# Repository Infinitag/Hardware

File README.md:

# INFINITAG Hardware

All hardware files for the INFINITAG laser tag system

## Credits
Website: <http://www.infinitag.io>

## License
All files are published under Creative Commons Attribution-NonCommercial-ShareAlike 4.0 International (CC BY-NC-SA 4.0) License
<https://creativecommons.org/licenses/by-nc-sa/4.0/>

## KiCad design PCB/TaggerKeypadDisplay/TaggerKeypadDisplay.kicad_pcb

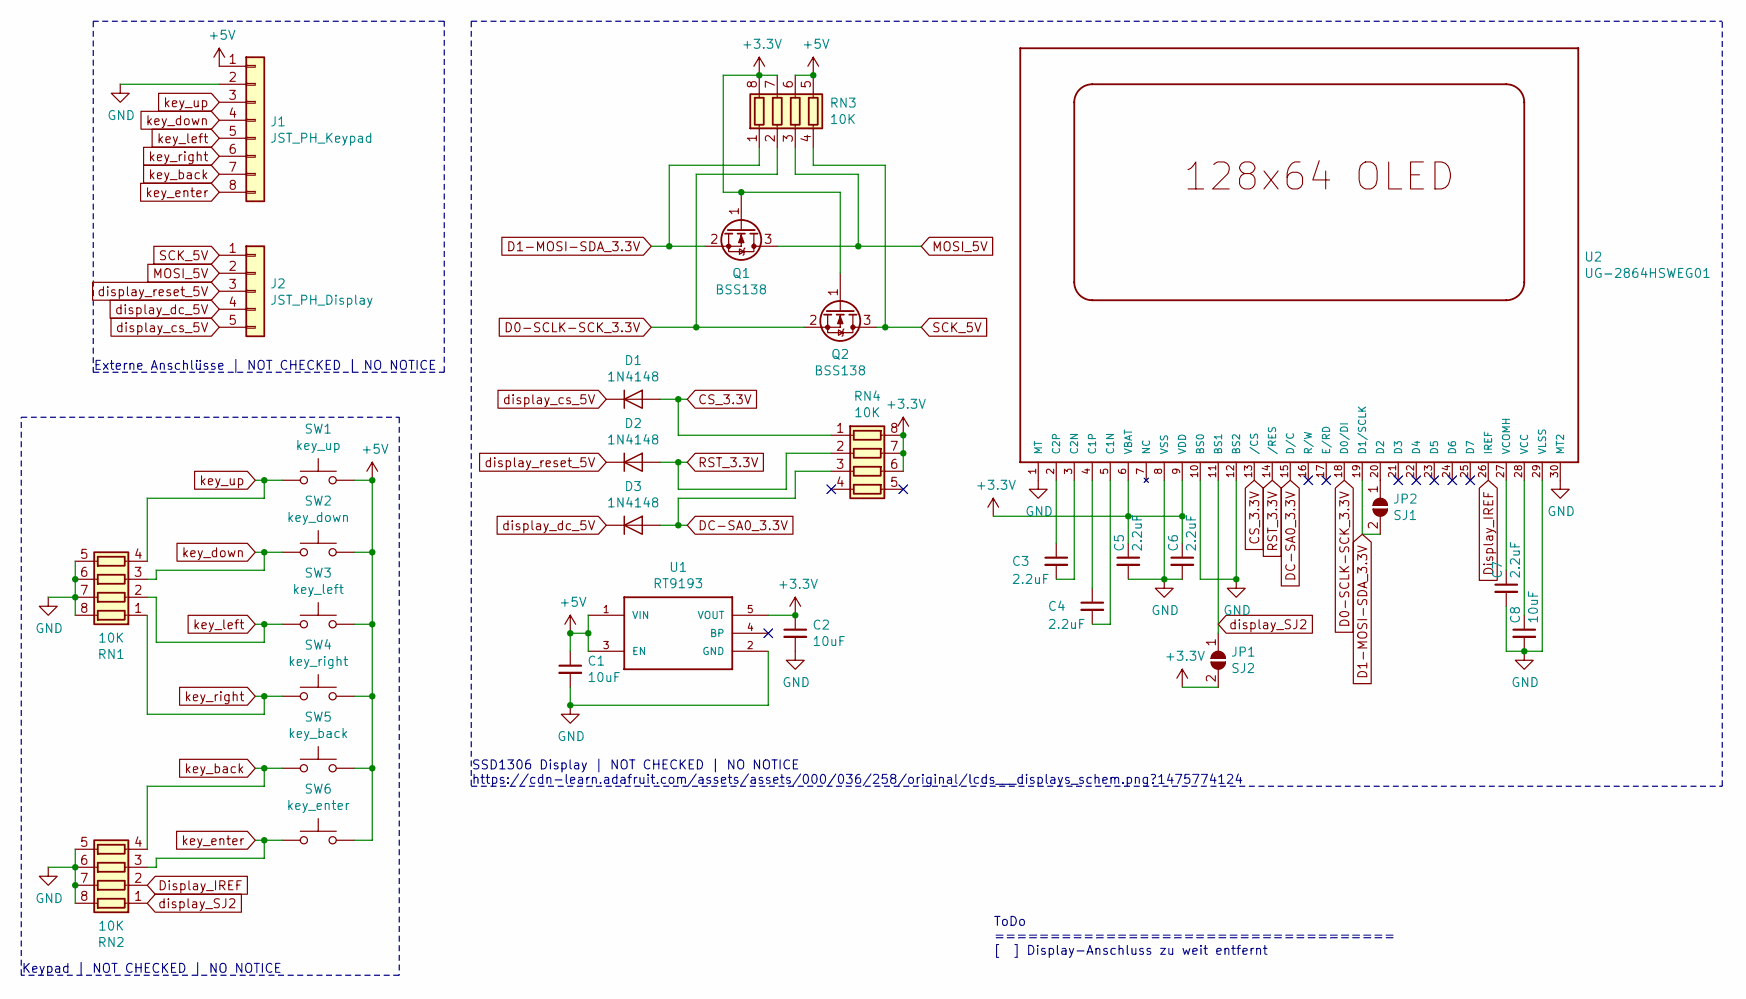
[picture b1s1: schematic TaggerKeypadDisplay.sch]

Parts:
C1, C2, C8: 10uF; C_0805_2012Metric
C3, C4, C5, C6, C7: 2.2uF; C_0805_2012Metric
D1, D2, D3: 1N4148; D_SOD-123
J1: JST_PH_Keypad; JST_PH_B8B-PH-K_1x08_P2.00mm_Vertical
J2: JST_PH_Display; JST_PH_B5B-PH-K_1x05_P2.00mm_Vertical
JP1: SJ2; SolderJumper-2_P1.3mm_Open_Pad1.0x1.5mm
JP2: SJ1; SolderJumper-2_P1.3mm_Open_Pad1.0x1.5mm
Q1, Q2: BSS138; SOT-23
RN1, RN2, RN3, RN4: 10K; R_Array_Convex_4x0603
SW1: key_up; Infinitag_Keypad_Button
SW2: key_down; Infinitag_Keypad_Button
SW3: key_left; Infinitag_Keypad_Button
SW4: key_right; Infinitag_Keypad_Button
SW5: key_back; Infinitag_Keypad_Button
SW6: key_enter; Infinitag_Keypad_Button
U1: RT9193; SOT94P279X129-5N
U2: UG-2864HSWEG01; 1X30-0.7MM

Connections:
+3V3: C2.1, C5.1, C6.1, JP1.2 (B), Q1.1 (G), Q2.1 (G), RN3.7 (R2.2), RN3.8 (R1.2), RN4.6 (R3.2), RN4.7 (R2.2), RN4.8 (R1.2), U1.5 (VOUT), U2.6 (VBAT), U2.9 (VDD)
+5V: C1.1, J1.1, RN3.5 (R4.2), RN3.6 (R3.2), SW1.2, SW2.2, SW3.2, SW4.2, SW5.2, SW6.2, U1.1 (VIN), U1.3 (EN)
CS_3.3V: D1.2 (A), RN4.1 (R1.1), U2.13 (/CS)
D0-SCLK-SCK_3.3V: Q2.2 (S), RN3.2 (R2.1), U2.18 (D0/DI)
D1-MOSI-SDA_3.3V: JP2.2 (B), Q1.2 (S), RN3.1 (R1.1), U2.19 (D1/SCLK)
DC-SA0_3.3V: D3.2 (A), RN4.3 (R3.1), U2.15 (D/C)
Display_IREF: RN2.2 (R2.1), U2.26 (IREF)
GND: C1.2, C2.2, C5.2, C6.2, C7.2, C8.2, J1.2, RN1.5 (R4.2), RN1.6 (R3.2), RN1.7 (R2.2), RN1.8 (R1.2), RN2.5 (R4.2), RN2.6 (R3.2), RN2.7 (R2.2), RN2.8 (R1.2), U1.2 (GND), U2.1 (MT), U2.8 (VSS), U2.10 (BS0), U2.12 (BS2), U2.29 (VLSS), U2.30 (MT2)
MOSI_5V: J2.2, Q1.3 (D), RN3.3 (R3.1)
unnamed: C3.1, U2.2 (C2P)
unnamed: C3.2, U2.3 (C2N)
unnamed: C4.1, U2.4 (C1P)
unnamed: C4.2, U2.5 (C1N)
unnamed: C7.1, U2.27 (VCOMH)
unnamed: C8.1, U2.28 (VCC)
unnamed: JP2.1 (A), U2.20 (D2)
RST_3.3V: D2.2 (A), RN4.2 (R2.1), U2.14 (/RES)
SCK_5V: J2.1, Q2.3 (D), RN3.4 (R4.1)
display_SJ2: JP1.1 (A), RN2.1 (R1.1), U2.11 (BS1)
display_cs_5V: D1.1 (K), J2.5
display_dc_5V: D3.1 (K), J2.4
display_reset_5V: D2.1 (K), J2.3
key_back: J1.7, RN2.4 (R4.1), SW5.1
key_down: J1.4, RN1.3 (R3.1), SW2.1
key_enter: J1.8, RN2.3 (R3.1), SW6.1
key_left: J1.5, RN1.2 (R2.1), SW3.1
key_right: J1.6, RN1.1 (R1.1), SW4.1
key_up: J1.3, RN1.4 (R4.1), SW1.1

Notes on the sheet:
Externe Anschlüsse | NOT CHECKED | NO NOTICE
SSD1306 Display | NOT CHECKED | NO NOTICE https://cdn-learn.adafruit.com/assets/assets/000/036/258/original/lcds___displays_schem.png?1475774124
Keypad | NOT CHECKED | NO NOTICE
ToDo ==================================== [ ] Display-Anschluss zu weit entfernt

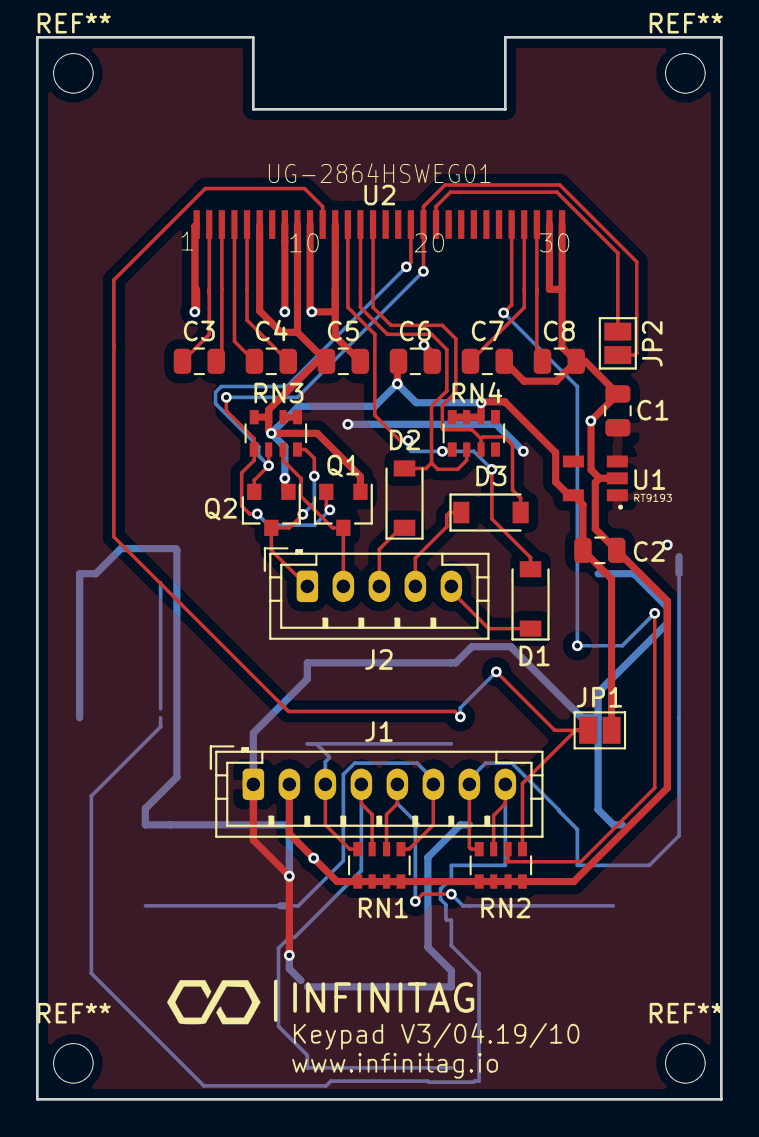
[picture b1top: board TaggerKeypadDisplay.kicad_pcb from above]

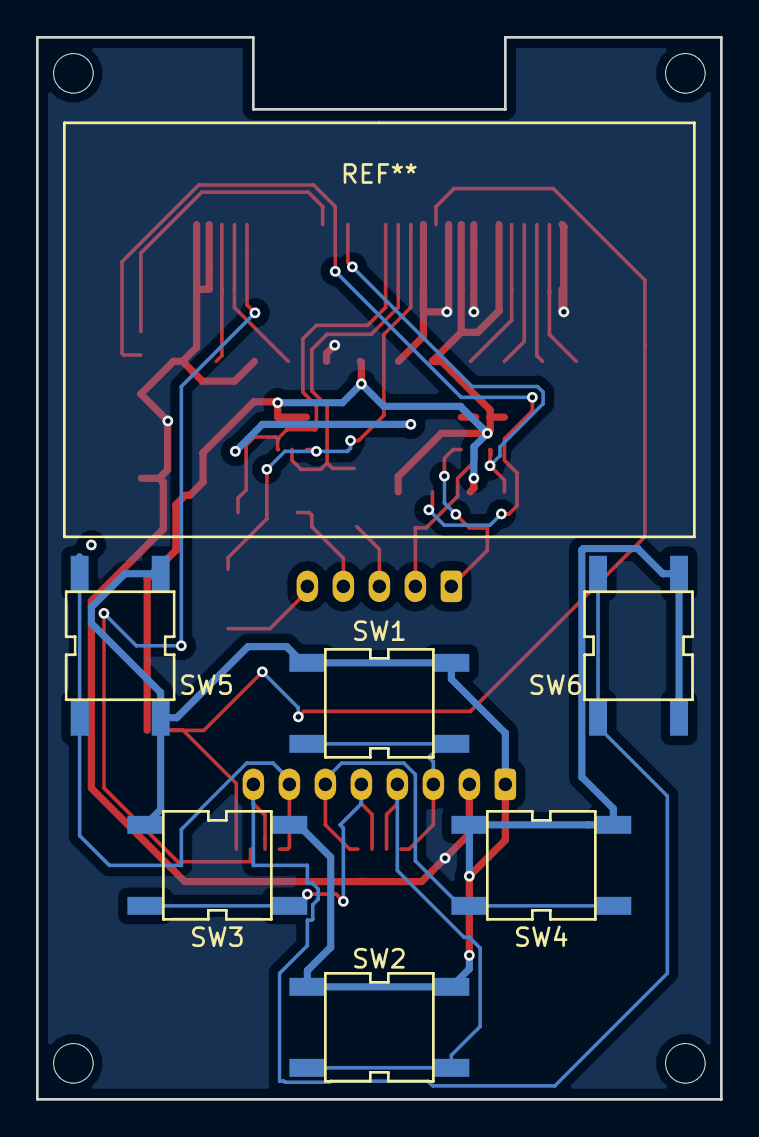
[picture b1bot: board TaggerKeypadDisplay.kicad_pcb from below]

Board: 2 copper layers, 38.0 x 59.0 mm, 29 parts (6 on the bottom side), 28 nets.

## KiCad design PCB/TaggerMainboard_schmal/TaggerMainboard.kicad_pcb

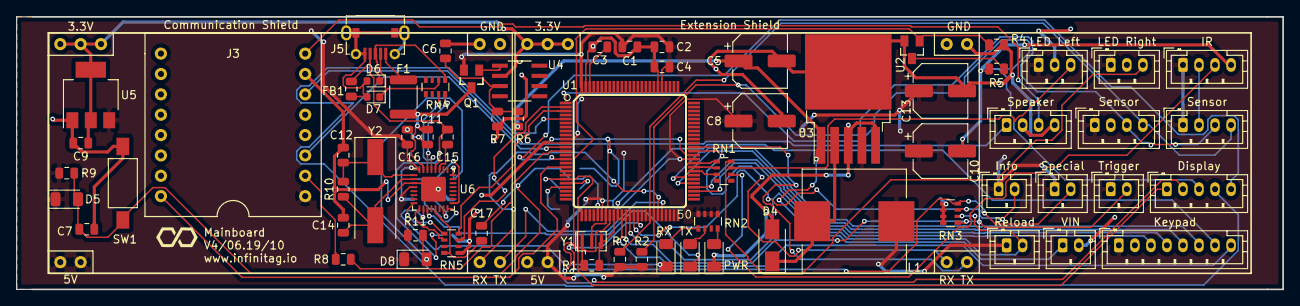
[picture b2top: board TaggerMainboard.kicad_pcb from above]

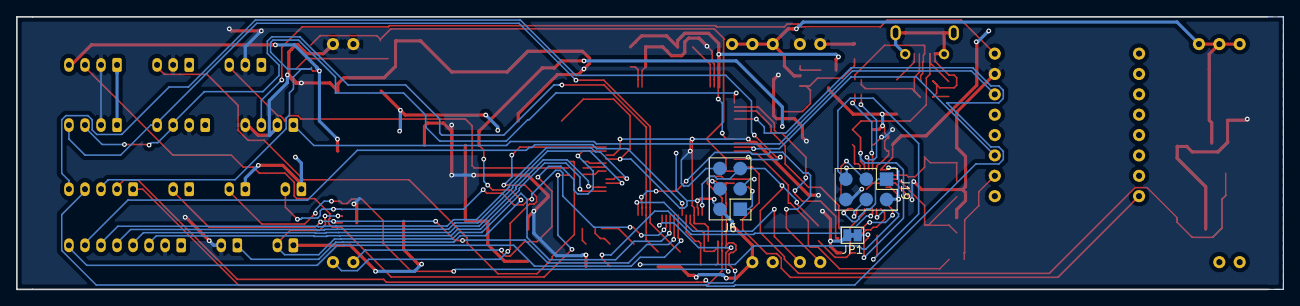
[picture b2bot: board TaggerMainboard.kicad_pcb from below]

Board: 2 copper layers, 158.0 x 34.0 mm, 74 parts (3 on the bottom side), 73 nets.

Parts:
C1, C2, C3, C4, C6, C17: 100nF; C_0805_2012Metric
C5, C8, C10, C13: 220uF/16V; CP_Elec_6.3x5.8
C7: 22pF; C_0805_2012Metric
C9: 10uF; C_0805_2012Metric
C11, C16: 100n; C_0805_2012Metric
C12, C14: 22p; C_0805_2012Metric
C15: 1u; C_0805_2012Metric
Communication Shield: WiFi Connector; Infinitag_ESP_Shield_Lang
D4: S534; D_SMA
D5, D8: CD1206-S01575; D_1206_3216Metric
D6, D7: CG0603MLC-05E; D_0603_1608Metric
Display: JST_PH_Display; JST_PH_B5B-PH-K_1x05_P2.00mm_Vertical
Extension Shield: Infinitag_ESP_Shield_Lang
F1: Poly 500mA; Fuse_1812_4532Metric
FB1: BLM21PG 221; L_0805_2012Metric
IR: JST_PH_IrLED; JST_PH_B4B-PH-K_1x04_P2.00mm_Vertical
Info: JST_PH_Info; JST_PH_B2B-PH-K_1x02_P2.00mm_Vertical
J3: DFPlayer
J5: USB_OTG; Micro USB Jack
J6: ICSP; ICSP_Pogo
J19: Conn_02x03_Odd_Even; ICSP_Pogo
JP1: SolderJumper_2_Bridged; SolderJumper-2_P1.3mm_Bridged_Pad1.0x1.5mm
Keypad: JST_PH_Keypad; JST_PH_B8B-PH-K_1x08_P2.00mm_Vertical
L1: 330uH; L_Wuerth_HCI-1350
LED Left: JST_PH_LEDbar_left; JST_PH_B3B-PH-K_1x03_P2.00mm_Vertical
LED Right: JST_PH_LEDbar_right; JST_PH_B3B-PH-K_1x03_P2.00mm_Vertical
PWR: LED_green; LED_1206_3216Metric
Q1: FDN304P; SSOT-3
R1, R10: 1M; R_0805_2012Metric
R2, R3, R4, R6, R7, R9, R11: 10K; R_0805_2012Metric
R5: 50 Ohm; R_0805_2012Metric
R8: 1K; R_0805_2012Metric
RN1: Array 470; R_Array_Convex_4x0603
RN2, RN3: Array 10K; R_Array_Convex_4x0603
RN4: 22R; R_Array_Convex_4x0603
RN5: 1K; R_Array_Convex_4x0603
RX: LED_RX_red; LED_1206_3216Metric
Reload: JST_PH_Reload; JST_PH_B2B-PH-K_1x02_P2.00mm_Vertical
SW1: SW_Reset; SW_SPST_FSMSM
Sensor: JSP_PH_Sensor; JST_PH_B4B-PH-K_1x04_P2.00mm_Vertical
Sensor#2: JSP_PH_Sensor; JST_PH_B4B-PH-K_1x04_P2.00mm_Vertical
Speaker: JST_PH_Speaker; JST_PH_B4B-PH-K_1x04_P2.00mm_Vertical
Special: JST_PH_Special; JST_PH_B2B-PH-K_1x02_P2.00mm_Vertical
TX: LED_TX_red; LED_1206_3216Metric
Trigger: JST_PH_Trigger; JST_PH_B2B-PH-K_1x02_P2.00mm_Vertical
U1: MCU-ATMEGA2560-16AU(TQFP100); TQFP100-0.5-14X14MM
U2: IRLML2502; SOT23
U3: LM2596S-5; TO-263-5_TabPin3
U4: LMV358; SOIC127P620X172-8N
U5: AMS1117-3.3; SOT-223-3_TabPin2
U6: ATmega16U2-MU; QFN-32-1EP_5x5mm_P0.5mm_EP3.1x3.1mm
VIN: VIN; JST_PH_B2B-PH-K_1x02_P2.00mm_Vertical
Y1: CSTCE16M0V53-R0; Resonator_SMD_muRata_CSTxExxV-3Pin_3.0x1.1mm
Y2: 16MHz; Crystal_SMD_HC49-SD

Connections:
+3V3: C9.1, Communication Shield.2, Extension Shield.2, U4.2, U5.2
+5V: C1.1, C2.1, C4.1, C8.1, C10.1, C13.1, C16.2, Communication Shield.1, D5.1, D8.1, Extension Shield.1, IR.1, Info.1, J3.1, J6.2, J19.2, Keypad.1, L1.2, LED Left.1, LED Right.1, Q1.2, R2.1, R3.2, R9.1, R11.2, RN2.5, RN2.6, RN2.7, RN2.8, Reload.1, Sensor.1, Sensor#2.1, Special.1, Trigger.1, U1.10, U1.31, U1.61, U1.80, U1.100, U3.4, U5.3, U6.4, U6.32
ATM_RX1: Communication Shield.4, U1.45
ATM_TX1: Communication Shield.5, U1.46
DF_BUSY: J3.16, U1.17
DF_RX: R8.1, U1.13
DF_SPK_LEFT: J3.6, Speaker.1
DF_SPK_RIGHT: J3.8, Speaker.3
DF_TX: J3.3, U1.12
GND: C1.2, C2.2, C3.2, C4.2, C5.2, C6.2, C7.2, C8.2, C9.2, C11.1, C12.2, C13.2, C14.2, C16.1, Communication Shield.3, D4.2, Extension Shield.3, IR.2, J3.7, J6.6, J19.6, JP1.2, Keypad.2, LED Left.2, LED Right.2, PWR.1, R4.2, R7.2, RN3.5, RN3.6, RN3.7, RN3.8, RN5.5, SW1.2, Sensor.2, Sensor#2.2, Speaker.2, Speaker.4, U1.11, U1.32, U1.62, U1.81, U1.99, U2.2, U3.3, U3.5, U5.1, U6.3, U6.33, VIN.2, Y1.2
IR_LED_GND: C10.2, IR.4, R5.1
IR_LED_SEND: R4.1, U1.18, U2.1
IR_SK_Data: IR.3, RN1.6
LED_RX: RX.1, U6.10
LED_TX: TX.1, U6.11
MISO: J6.1, U1.22
MOSI: Display.2, J6.4, U1.21
unnamed: C3.1, U1.98
unnamed: C6.1, R6.2, R7.1, U4.3
unnamed: C12.1, R10.1, U6.1, Y2.1
unnamed: C14.1, R10.2, U6.2, Y2.2
unnamed: C15.1, U6.27
unnamed: C15.2, FB1.1, J5.4, JP1.1, U6.28
unnamed: C17.2, RN5.4, U6.13
unnamed: RN2.1, RX.2
unnamed: RN2.2, TX.2
unnamed: PWR.2, RN2.4
unnamed: D4.1, L1.1, U3.2
unnamed: D6.1, J5.3, RN4.1
unnamed: D6.2, D7.2, FB1.2, J5.5, J5.6
unnamed: D7.1, J5.2, RN4.2
unnamed: D8.2, J19.5, R11.1, U6.24
unnamed: F1.2, J5.1
unnamed: J3.2, R8.2
unnamed: J19.1, U6.16
unnamed: J19.3, U6.17
unnamed: J19.4, U6.15
unnamed: Q1.1, U4.1
unnamed: R1.1, U1.33, Y1.1
unnamed: R1.2, U1.34, Y1.3
unnamed: R5.2, U2.3
unnamed: RN1.1, U1.60
unnamed: RN1.2, U1.59
unnamed: RN1.3, U1.58
unnamed: RN4.7, U6.29
unnamed: RN4.8, U6.30
unnamed: RN5.1, U6.8
unnamed: RN5.2, U6.9
RESET: C7.1, C17.1, D5.2, J6.5, R9.2, SW1.1, U1.30
RX0: RN5.7, U1.2
SCK: Display.1, J6.3, U1.20
SCL: R3.1, Sensor.4, Sensor#2.4, U1.43
SDA: R2.2, Sensor.3, Sensor#2.3, U1.44
Shield_RX: Extension Shield.4, U1.63
Shield_TX: Extension Shield.5, U1.64
TX0: RN5.8, U1.3
VBUS: C11.2, F1.1, Q1.3, U6.31
VIN_on: C5.1, R6.1, U3.1, VIN.1
display_cs: Display.5, U1.15
display_dc: Display.4, U1.5
display_reset: Display.3, U1.1
key_back: Keypad.7, U1.35
key_down: Keypad.4, U1.54
key_enter: Keypad.8, U1.36
key_info: Info.2, RN3.3, U1.39
key_left: Keypad.5, U1.55
key_reload: RN3.2, Reload.2, U1.38
key_right: Keypad.6, U1.56
key_special: RN3.4, Special.2, U1.40
key_trigger: RN3.1, Trigger.2, U1.37
key_up: Keypad.3, U1.53
ledbar_left: LED Left.3, RN1.7
ledbar_right: LED Right.3, RN1.8

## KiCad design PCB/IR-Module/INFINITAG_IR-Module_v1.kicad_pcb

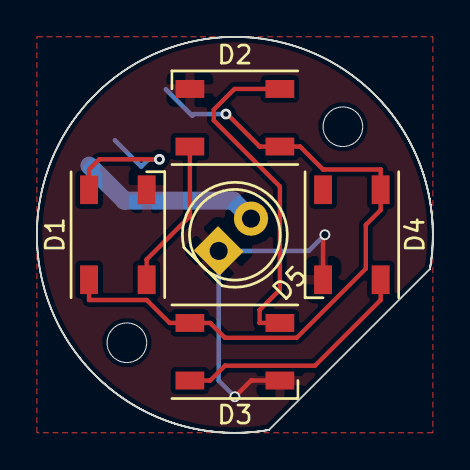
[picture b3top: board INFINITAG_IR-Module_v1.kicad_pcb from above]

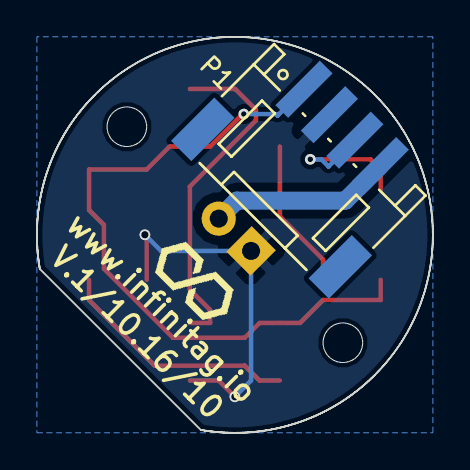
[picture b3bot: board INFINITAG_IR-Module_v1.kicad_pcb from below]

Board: 2 copper layers, 22.0 x 22.0 mm, 9 parts (2 on the bottom side), 7 nets.

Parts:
D1, D2, D3, D4: SK6812; LED_WS2812B-PLCC4
D5: LED; LED-5MM
LOGO: INFINITAG_LOGO_6mm
P1: CONN_01X04; JST_PH_S4B-PH-SM4-TB_04x2.00mm_Angled
REF1, REF2: MountingHole_2.2mm_M2

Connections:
+5V: D1.1, D2.1, D3.1, D4.1, P1.1
/IR: D5.2, P1.4
GND: D1.3, D2.3, D3.3, D4.3, D5.1, P1.2
unnamed: D1.2, D2.4
unnamed: D1.4, P1.3
unnamed: D2.2, D3.4
unnamed: D3.2, D4.4

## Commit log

2016-11-13 3D Dateien für das Sensorgehäuse
2016-11-13 Einfache Readme hinzugefügt
2016-11-22 IR-Module Files
2017-01-22 lens test equipment for 3D printing
2017-01-22 IR Target
2017-08-02 DesktopKit
2019-03-10 Libs hinzugefügt
2019-03-10 Tagger Mainboard
2019-03-10 Footprints für Anschlüsse hinterlegt
2019-03-10 LED + Kondensatoren (keine CP) mit Footprint hinterlegt
2019-03-10 Footprints für Widerstände
2019-03-10 Footprints für CP Kondensatoren hinzugefügt
2019-03-10 Footprints für Push Buttons
2019-03-10 Diverse Footprints hinzugefügt
2019-03-16 VIN ersetzt + WiFi Entfernt + WiFi Header hinzugefügt
2019-03-16 Keypad ohne Widerstände auf dem Board
2019-03-16 Notiz am Atmega angepasst
2019-03-16 LMV hinzugefügt
2019-03-16 Footsprints zugewiesen
2019-03-18 Footprints angepasst
2019-03-24 Schematic fertiggestellt, Libs hinzugefügt, PCB Design erstellt
2019-03-24 Keypad + Bohrungen + Logo & Co
2019-03-24 Anpassungen
2019-04-28 Schmale Version des Boards
